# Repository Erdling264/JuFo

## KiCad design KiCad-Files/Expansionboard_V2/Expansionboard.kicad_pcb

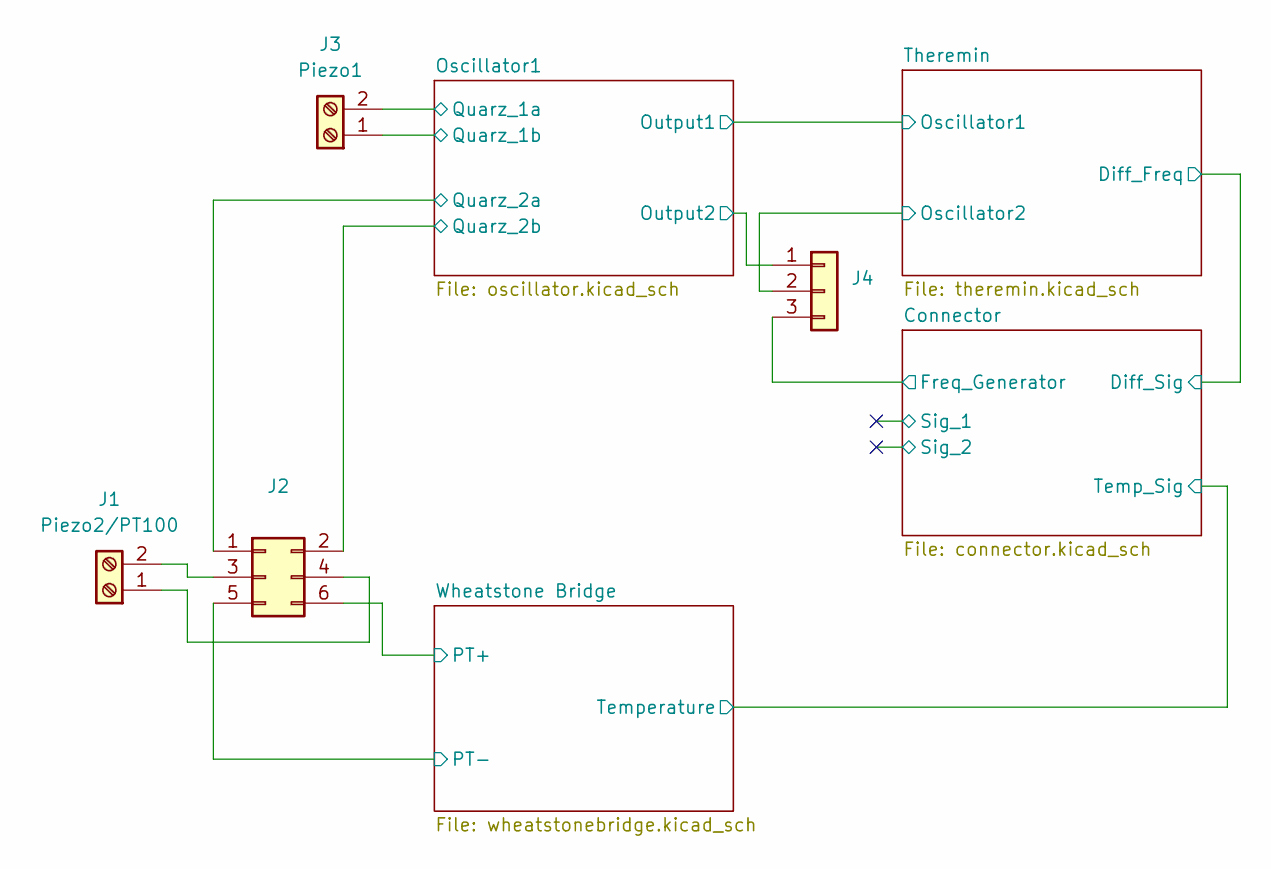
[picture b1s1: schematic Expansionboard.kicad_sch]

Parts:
J1: Piezo2/PT100; TerminalBlock_bornier-2_P5.08mm
J2: Conn_02x03_Odd_Even; PinHeader_2x03_P2.54mm_Vertical
J3: Piezo1; TerminalBlock_bornier-2_P5.08mm
J4: Conn_01x03; PinHeader_1x03_P2.54mm_Vertical

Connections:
/Connector/Freq_Generator: J4.3; also elsewhere on the board
/Oscillator1/Output2: J4.1; also elsewhere on the board
/Oscillator1/Quarz_1a: J3.2; also elsewhere on the board
/Oscillator1/Quarz_1b: J3.1; also elsewhere on the board
/Oscillator1/Quarz_2a: J2.1; also elsewhere on the board
/Oscillator1/Quarz_2b: J2.2; also elsewhere on the board
/Theremin/Oscillator2: J4.2; also elsewhere on the board
/Wheatstone Bridge/PT+: J2.6; also elsewhere on the board
unnamed: J1.1, J2.4
unnamed: J1.2, J2.3
VREF: J2.5; also elsewhere on the board

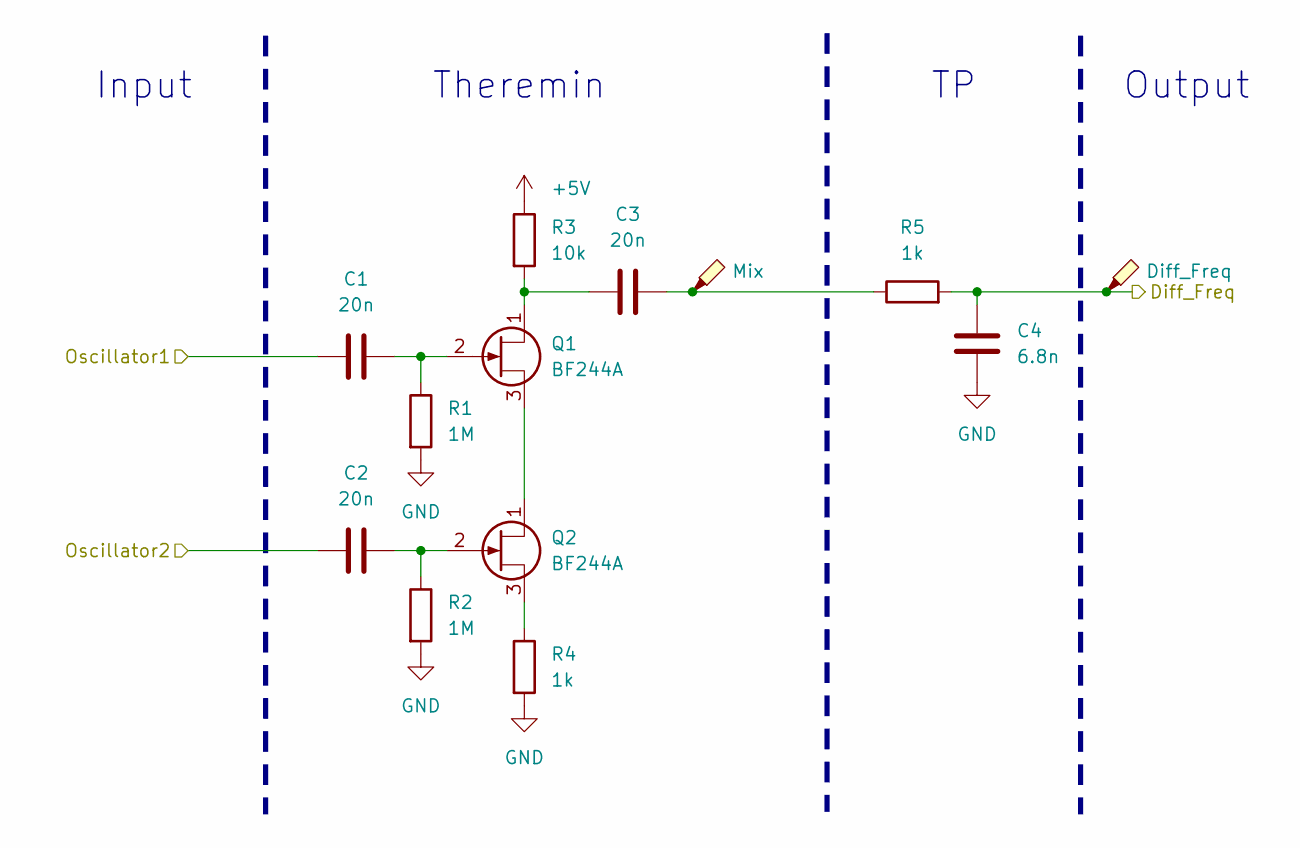
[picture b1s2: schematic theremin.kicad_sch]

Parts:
C1, C2, C3: 20n; C_Disc_D6.0mm_W2.5mm_P5.00mm
C4: 6.8n; C_Disc_D6.0mm_W2.5mm_P5.00mm
Q1, Q2: BF244A; TO-92_Inline
R1, R2: 1M; R_Axial_DIN0207_L6.3mm_D2.5mm_P10.16mm_Horizontal
R3: 10k; R_Axial_DIN0207_L6.3mm_D2.5mm_P10.16mm_Horizontal
R4, R5: 1k; R_Axial_DIN0207_L6.3mm_D2.5mm_P10.16mm_Horizontal
TP1: Mix; TestPoint_Loop_D2.60mm_Drill0.9mm_Beaded
TP2: Diff_Freq; TestPoint_Loop_D2.60mm_Drill0.9mm_Beaded

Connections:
+5V: R3.1; also elsewhere on the board
/Connector/Diff_Sig: C4.2, R5.2, TP2.1; also elsewhere on the board
/Oscillator1/Output1: C1.1; also elsewhere on the board
/Theremin/Oscillator2: C2.1; also elsewhere on the board
GND: C4.1, R1.2, R2.2, R4.2; also elsewhere on the board
unnamed: C3.2, R5.1, TP1.1
unnamed: C3.1, Q1.1 (D), R3.2
unnamed: C1.2, Q1.2 (G), R1.1
unnamed: Q1.3 (S), Q2.1 (D)
unnamed: C2.2, Q2.2 (G), R2.1
unnamed: Q2.3 (S), R4.1

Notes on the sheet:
Theremin
Output
Input

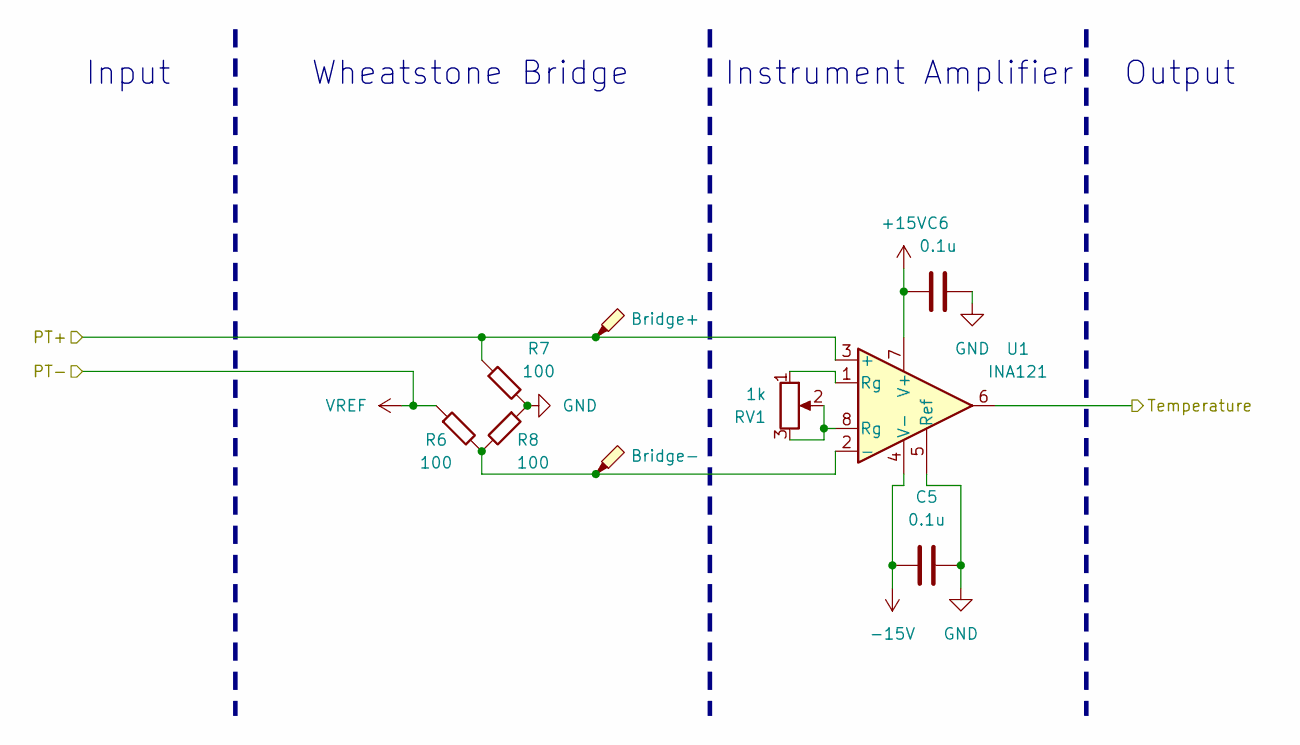
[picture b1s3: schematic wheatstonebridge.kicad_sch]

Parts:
C5, C6: 0.1u; C_Disc_D6.0mm_W2.5mm_P5.00mm
R6, R7, R8: 100; R_Axial_DIN0207_L6.3mm_D2.5mm_P10.16mm_Horizontal
RV1: 1k; Potentiometer_Bourns_3009P_Horizontal
TP3: Bridge+; TestPoint_Loop_D2.60mm_Drill0.9mm_Beaded
TP4: Bridge-; TestPoint_Loop_D2.60mm_Drill0.9mm_Beaded
U1: INA121; DIP-8_W7.62mm_Socket

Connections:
+15V: C6.1, U1.7 (V+); also elsewhere on the board
-15V: C5.1, U1.4 (V-); also elsewhere on the board
/Connector/Temp_Sig: U1.6; also elsewhere on the board
/Wheatstone Bridge/PT+: R7.1, TP3.1, U1.3 (+); also elsewhere on the board
GND: C5.2, C6.2, R7.2, R8.1, U1.5 (Ref); also elsewhere on the board
unnamed: RV1.1, U1.1 (Rg)
unnamed: RV1.2, RV1.3, U1.8 (Rg)
unnamed: R6.2, R8.2, TP4.1, U1.2 (-)
VREF: R6.1; also elsewhere on the board

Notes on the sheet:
Input
Output
Instrument Amplifier
Wheatstone Bridge

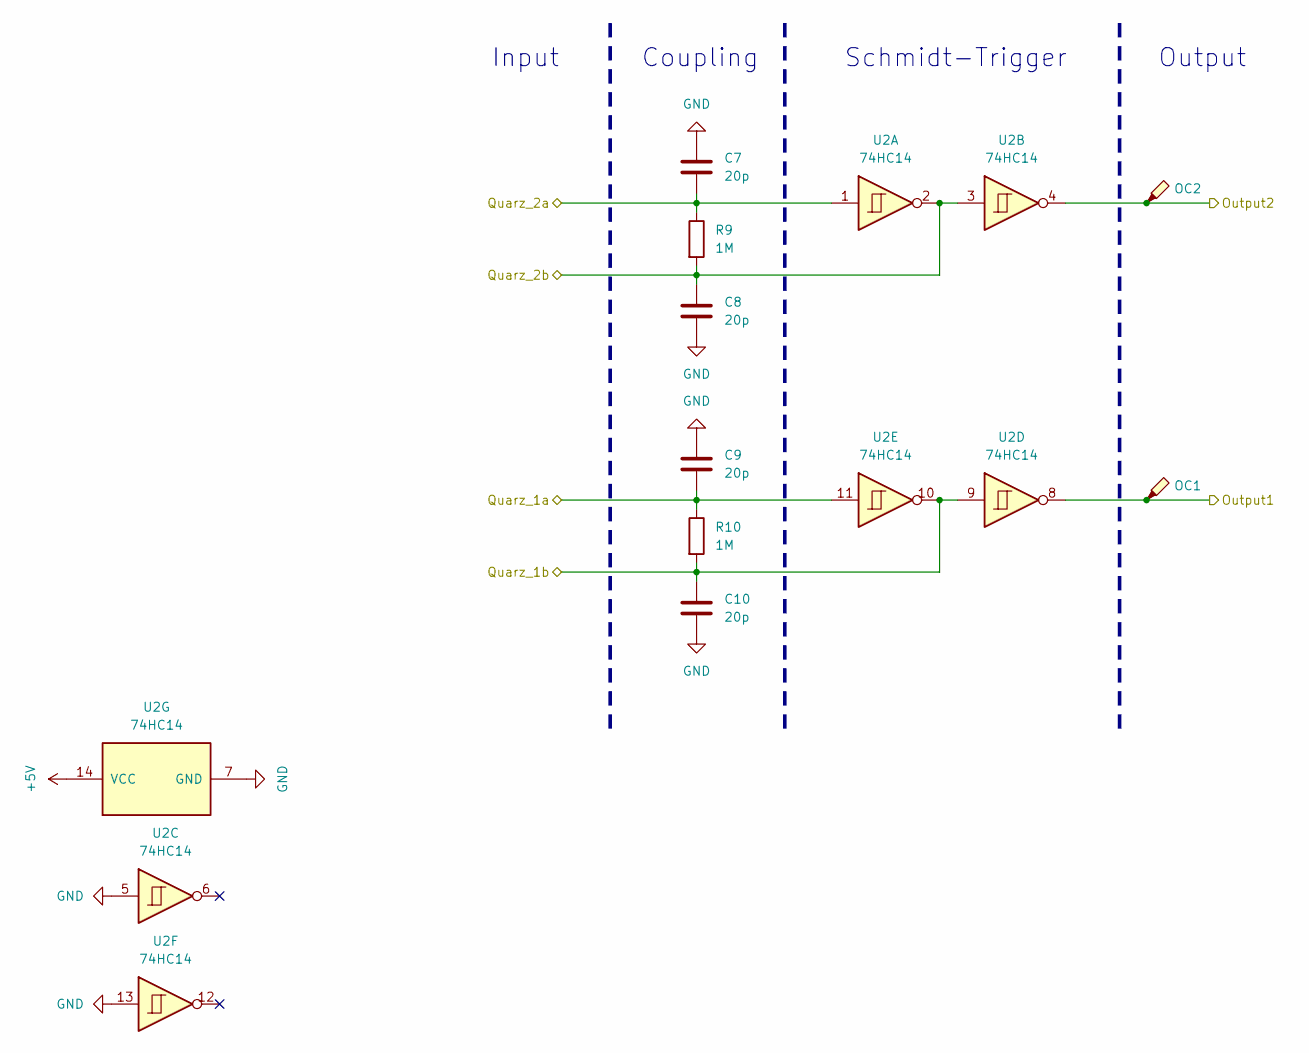
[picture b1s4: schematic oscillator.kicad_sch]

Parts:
C7, C8, C9, C10: 20p; C_Disc_D6.0mm_W2.5mm_P5.00mm
R9, R10: 1M; R_Axial_DIN0207_L6.3mm_D2.5mm_P10.16mm_Horizontal
TP5: OC1; TestPoint_Loop_D2.60mm_Drill0.9mm_Beaded
TP6: OC2; TestPoint_Loop_D2.60mm_Drill0.9mm_Beaded
U2: 74HC14; DIP-14_W7.62mm_Socket

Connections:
+5V: U2.14 (VCC); also elsewhere on the board
/Oscillator1/Output1: TP5.1, U2.8; also elsewhere on the board
/Oscillator1/Output2: TP6.1, U2.4; also elsewhere on the board
/Oscillator1/Quarz_1a: C9.1, R10.1, U2.11; also elsewhere on the board
/Oscillator1/Quarz_1b: C10.2, R10.2, U2.9, U2.10; also elsewhere on the board
/Oscillator1/Quarz_2a: C7.1, R9.1, U2.1; also elsewhere on the board
/Oscillator1/Quarz_2b: C8.2, R9.2, U2.2, U2.3; also elsewhere on the board
GND: C7.2, C8.1, C9.2, C10.1, U2.5, U2.7 (GND), U2.13; also elsewhere on the board

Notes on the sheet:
Schmidt-Trigger
Input
Coupling
Output

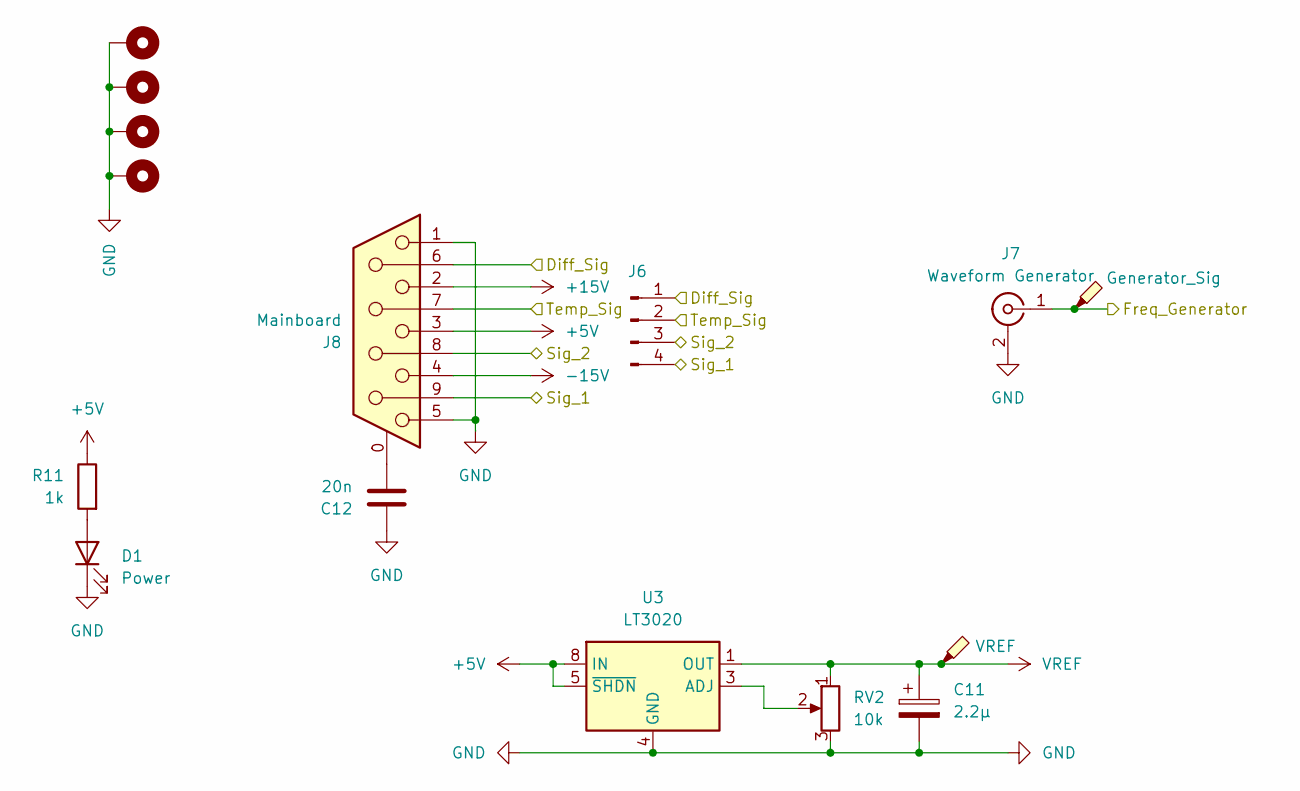
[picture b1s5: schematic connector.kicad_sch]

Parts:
C11: 2.2µ; CP_Radial_D5.0mm_P2.50mm
C12: 20n; C_Disc_D6.0mm_W2.5mm_P5.00mm
D1: Power; LED_D3.0mm_Clear
H1, H2, H3, H4: MountingHole_Pad; MountingHole_4.3mm_M4_DIN965_Pad_TopBottom
J6: Conn_01x04_Pin; PinHeader_1x04_P2.54mm_Vertical
J7: Waveform Generator; BNC_Amphenol_B6252HB-NPP3G-50_Horizontal
J8: Mainboard; DSUB-9_Female_Horizontal_P2.77x2.84mm_EdgePinOffset7.70mm_H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
R11: 1k; R_Axial_DIN0207_L6.3mm_D2.5mm_P10.16mm_Horizontal
RV2: 10k; Potentiometer_Bourns_3009P_Horizontal
TP7: VREF; TestPoint_Loop_D2.60mm_Drill0.9mm_Beaded
TP8: Generator_Sig; TestPoint_Loop_D2.60mm_Drill0.9mm_Beaded
U3: LT3020; MSOP-8-1EP_3x3mm_P0.65mm_EP1.73x1.85mm_ThermalVias

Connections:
+5V: J8.3, R11.1, U3.5 (~SHDN), U3.7 (IN), U3.8 (IN); also elsewhere on the board
+15V: J8.2; also elsewhere on the board
-15V: J8.4; also elsewhere on the board
/Connector/Diff_Sig: J6.1, J8.6; also elsewhere on the board
/Connector/Freq_Generator: J7.1 (In), TP8.1; also elsewhere on the board
/Connector/Sig_1: J6.4, J8.9
/Connector/Sig_2: J6.3, J8.8
/Connector/Temp_Sig: J6.2, J8.7; also elsewhere on the board
GND: C11.2, C12.2, D1.1 (K), H1.1, H2.1, H3.1, H4.1, J7.2 (Ext), J8.1, J8.5, RV2.3, U3.4 (GND), U3.9 (GND); also elsewhere on the board
unnamed: D1.2 (A), R11.2
unnamed: C12.1, J8.0 (PAD)
unnamed: RV2.2, U3.3 (ADJ)
VREF: C11.1, RV2.1, TP7.1, U3.1 (OUT), U3.2 (OUT); also elsewhere on the board

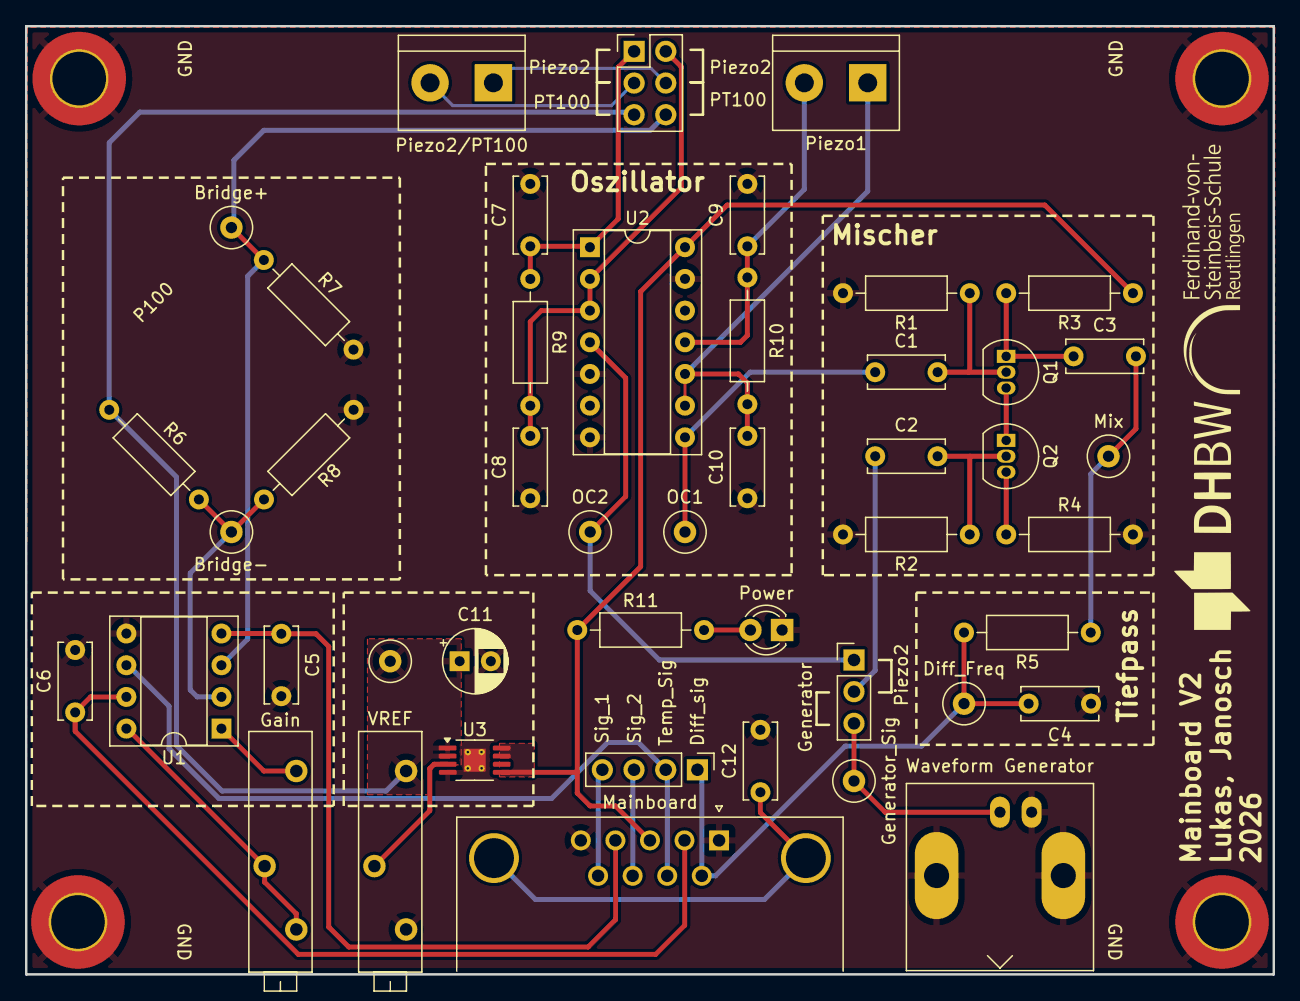
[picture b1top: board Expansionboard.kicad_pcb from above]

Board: 2 copper layers, 100.0 x 76.0 mm, 50 parts (0 on the bottom side), 32 nets.

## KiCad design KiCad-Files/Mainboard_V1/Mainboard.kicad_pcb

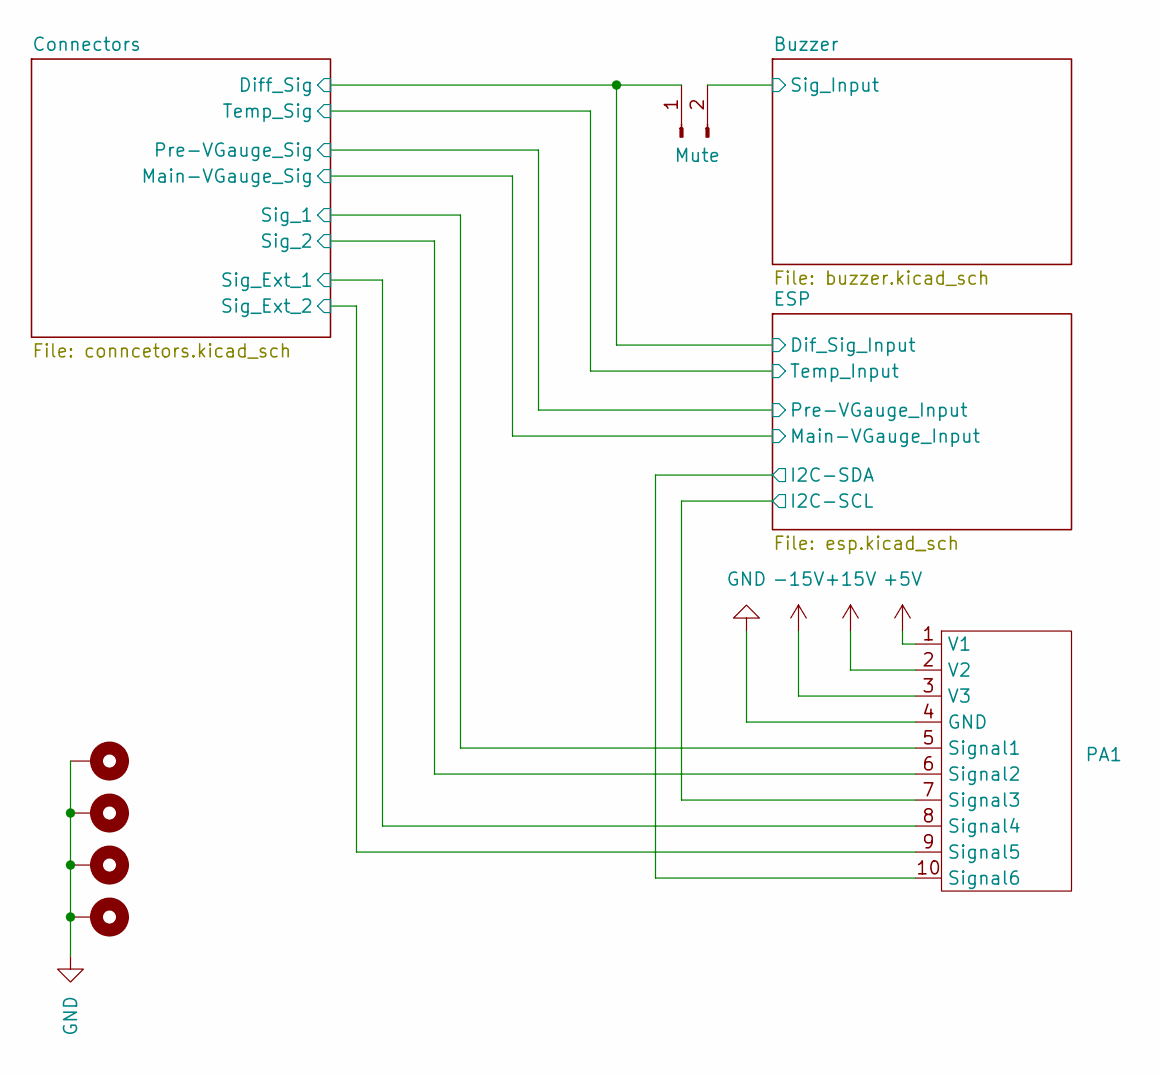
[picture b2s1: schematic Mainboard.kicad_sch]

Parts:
H1, H2, H3, H4: MountingHole_Pad; MountingHole_4.3mm_M4_DIN965_Pad_TopBottom
J1: Mute; PinSocket_1x02_P2.54mm_Vertical
PA1: Prototyping_Area

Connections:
+5V: PA1.1 (V1); also elsewhere on the board
+15V: PA1.2 (V2); also elsewhere on the board
-15V: PA1.3 (V3); also elsewhere on the board
/Buzzer/Sig_Input: J1.2; also elsewhere on the board
/Connectors/Diff_Sig: J1.1; also elsewhere on the board
/Connectors/Sig_1: PA1.5 (Signal1); also elsewhere on the board
/Connectors/Sig_2: PA1.6 (Signal2); also elsewhere on the board
/Connectors/Sig_Ext_1: PA1.8 (Signal4); also elsewhere on the board
/Connectors/Sig_Ext_2: PA1.9 (Signal5); also elsewhere on the board
/ESP/I2C-SCL: PA1.7 (Signal3); also elsewhere on the board
/ESP/I2C-SDA: PA1.10 (Signal6); also elsewhere on the board
GND: H1.1, H2.1, H3.1, H4.1, PA1.4 (GND); also elsewhere on the board

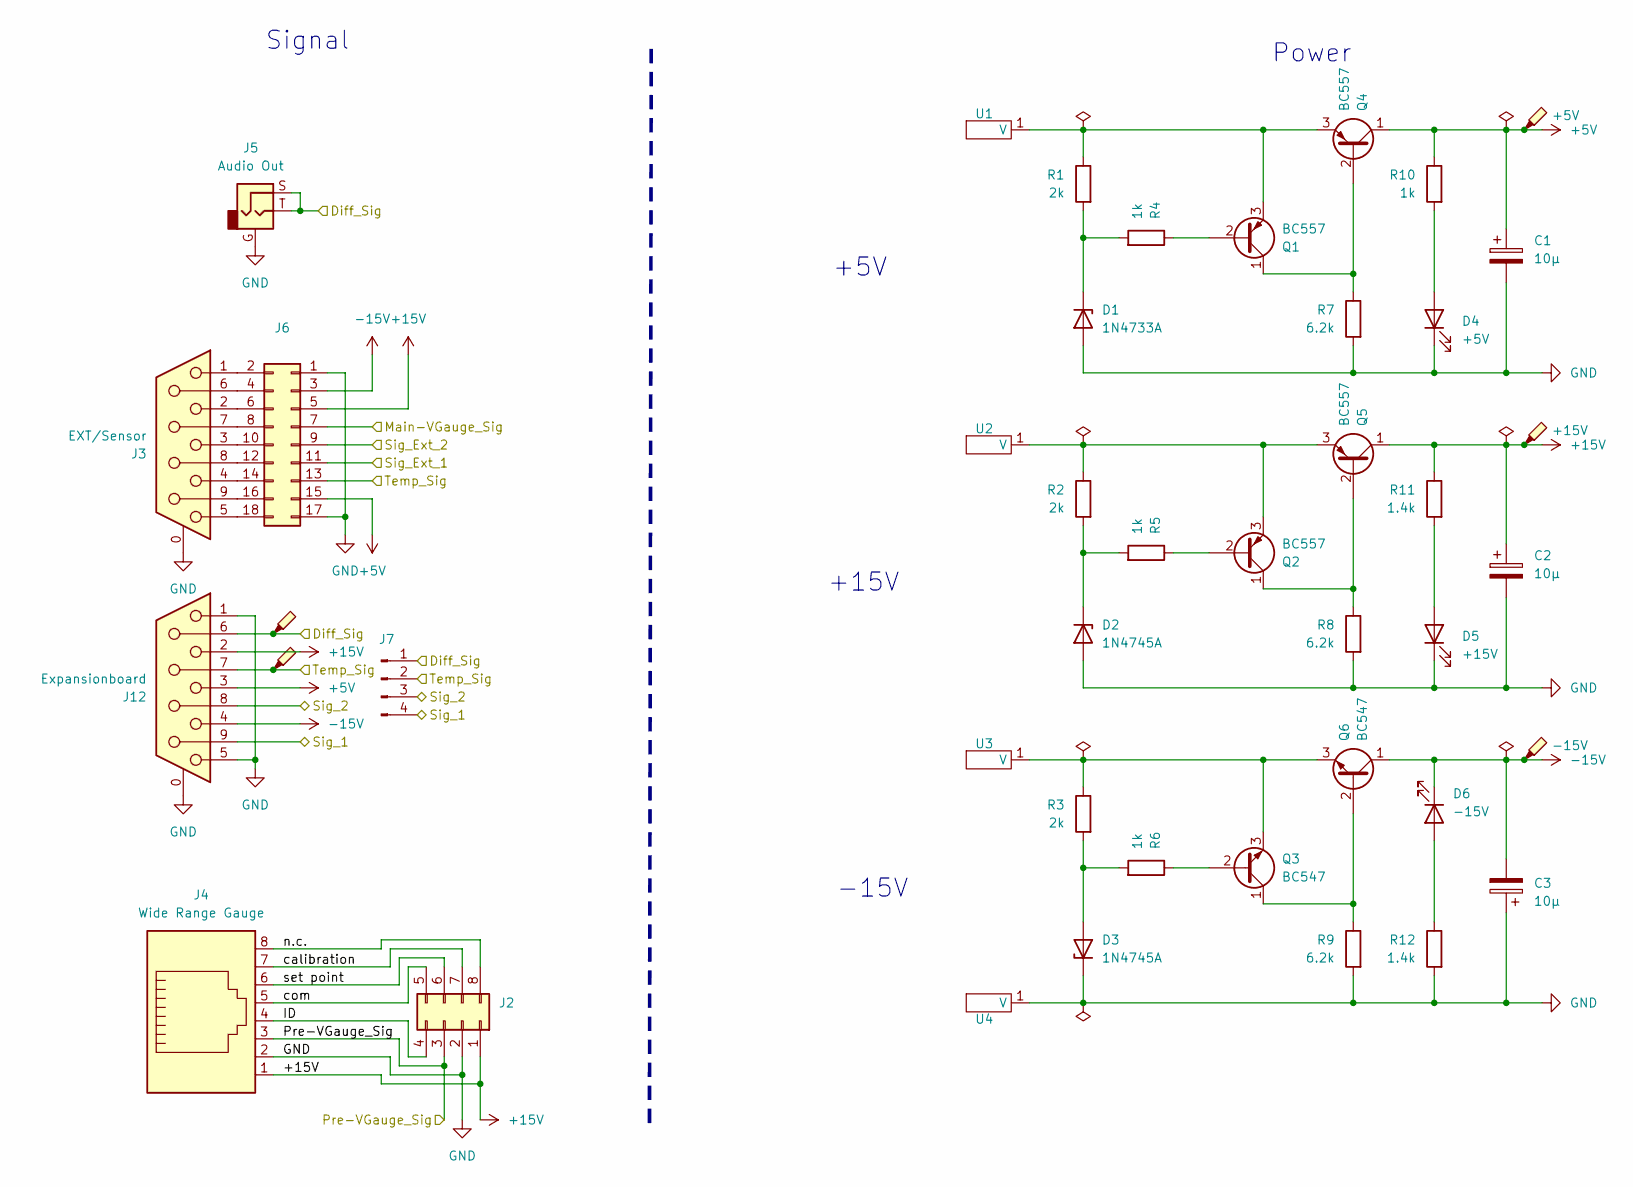
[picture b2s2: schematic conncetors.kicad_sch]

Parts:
C1, C2, C3: 10µ; CP_Radial_D4.0mm_P1.50mm
D1: 1N4733A; D_DO-41_SOD81_P10.16mm_Horizontal
D2, D3: 1N4745A; D_DO-41_SOD81_P10.16mm_Horizontal
D4: +5V; LED_D3.0mm_Clear
D5: +15V; LED_D3.0mm_Clear
D6: -15V; LED_D3.0mm_Clear
J2: Conn_02x04_Counter_Clockwise; PinHeader_2x04_P2.54mm_Vertical
J3: EXT/Sensor; DSUB-9_Female_Horizontal_P2.77x2.84mm_EdgePinOffset7.70mm_H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
J4: Wide Range Gauge; RJ45_OST_PJ012-8P8CX_Vertical
J5: Audio Out; Jack_3.5mm_CUI_SJ1-3523N_Horizontal
J6: Conn_02x09_Odd_Even; PinHeader_2x09_P2.54mm_Vertical
J7: Conn_01x04_Pin; PinHeader_1x04_P2.54mm_Vertical
J12: Expansionboard; DSUB-9_Female_Horizontal_P2.77x2.84mm_EdgePinOffset7.70mm_H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
Q1, Q2, Q4, Q5: BC557; TO-92_Inline
Q3, Q6: BC547; TO-92_Inline
R1, R2, R3: 2k; R_Axial_DIN0207_L6.3mm_D2.5mm_P10.16mm_Horizontal
R4, R5, R6, R10: 1k; R_Axial_DIN0207_L6.3mm_D2.5mm_P10.16mm_Horizontal
R7, R8, R9: 6.2k; R_Axial_DIN0207_L6.3mm_D2.5mm_P10.16mm_Horizontal
R11, R12: 1.4k; R_Axial_DIN0207_L6.3mm_D2.5mm_P10.16mm_Horizontal
TP1: Diff_Sig; TestPoint_Loop_D2.60mm_Drill0.9mm_Beaded
TP2: Temp_Sig; TestPoint_Loop_D2.60mm_Drill0.9mm_Beaded
TP3: +5V; TestPoint_Loop_D2.60mm_Drill0.9mm_Beaded
TP4: +15V; TestPoint_Loop_D2.60mm_Drill0.9mm_Beaded
TP5: -15V; TestPoint_Loop_D2.60mm_Drill0.9mm_Beaded
U1, U2: Banana_Cliff_FCR7350R_S16N-PC_Horizontal
U3: Banana_Cliff_FCR7350L_S16N-PC_Horizontal
U4: Banana_Cliff_FCR7350B_S16N-PC_Horizontal

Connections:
+5V: C1.1, J6.15, J12.3, Q4.1 (C), R10.1, TP3.1; also elsewhere on the board
+15V: C2.1, J2.1, J4.1, J6.5, J12.2, Q5.1 (C), R11.1, TP4.1; also elsewhere on the board
-15V: C3.2, D6.1 (K), J6.3, J12.4, Q6.1 (C), TP5.1; also elsewhere on the board
/Connectors/Diff_Sig: J5.S, J5.T, J7.1, J12.6, TP1.1; also elsewhere on the board
/Connectors/ID: J2.4, J4.4
/Connectors/Main-VGauge_Sig: J6.7; also elsewhere on the board
/Connectors/Pre-VGauge_Sig: J2.3, J4.3; also elsewhere on the board
/Connectors/Sig_1: J7.4, J12.9; also elsewhere on the board
/Connectors/Sig_2: J7.3, J12.8; also elsewhere on the board
/Connectors/Sig_Ext_1: J6.11; also elsewhere on the board
/Connectors/Sig_Ext_2: J6.9; also elsewhere on the board
/Connectors/Temp_Sig: J6.13, J7.2, J12.7, TP2.1; also elsewhere on the board
/Connectors/calibration: J2.7, J4.7
/Connectors/com: J2.5, J4.5
/Connectors/n.c.: J2.8, J4.8
/Connectors/set point: J2.6, J4.6
GND: C1.2, C2.2, C3.1, D1.2 (A), D2.2 (A), D3.1 (K), D4.1 (K), D5.1 (K), J2.2, J3.0 (PAD), J4.2, J5.G, J6.1, J6.17, J12.0 (PAD), J12.1, J12.5, R7.2, R8.2, R9.2, R12.2, U4.1 (V); also elsewhere on the board
unnamed: D1.1 (K), R1.2, R4.2
unnamed: D2.1 (K), R2.2, R5.2
unnamed: D3.2 (A), R3.2, R6.2
unnamed: D4.2 (A), R10.2
unnamed: D5.2 (A), R11.2
unnamed: D6.2 (A), R12.1
unnamed: J3.1, J6.2
unnamed: J3.6, J6.4
unnamed: J3.2, J6.6
unnamed: J3.7, J6.8
unnamed: J3.3, J6.10
unnamed: J3.8, J6.12
unnamed: J3.4, J6.14
unnamed: J3.9, J6.16
unnamed: J3.5, J6.18
unnamed: Q1.2 (B), R4.1
unnamed: Q1.1 (C), Q4.2 (B), R7.1
unnamed: Q1.3 (E), Q4.3 (E), R1.1, U1.1 (V)
unnamed: Q2.2 (B), R5.1
unnamed: Q2.1 (C), Q5.2 (B), R8.1
unnamed: Q2.3 (E), Q5.3 (E), R2.1, U2.1 (V)
unnamed: Q3.2 (B), R6.1
unnamed: Q3.1 (C), Q6.2 (B), R9.1
unnamed: Q3.3 (E), Q6.3 (E), R3.1, U3.1 (V)

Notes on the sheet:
+5V
+15V
Signal
Power
-15V

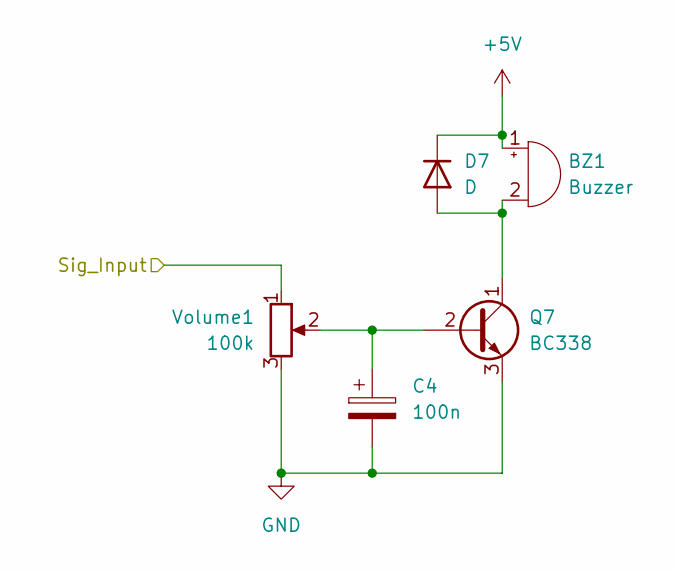
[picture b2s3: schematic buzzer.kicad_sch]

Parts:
BZ1: Buzzer; Buzzer_TDK_PS1240P02BT_D12.2mm_H6.5mm
C4: 100n; CP_Radial_D4.0mm_P1.50mm
D7: D; D_T-1_P10.16mm_Horizontal
Q7: BC338; TO-92
Volume1: 100k; Potentiometer_Omeg_PC16BU_Horizontal

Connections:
+5V: BZ1.1 (+), D7.1 (K); also elsewhere on the board
/Buzzer/Sig_Input: Volume1.1; also elsewhere on the board
GND: C4.2, Q7.3 (E), Volume1.3; also elsewhere on the board
unnamed: BZ1.2 (-), D7.2 (A), Q7.1 (C)
unnamed: C4.1, Q7.2 (B), Volume1.2

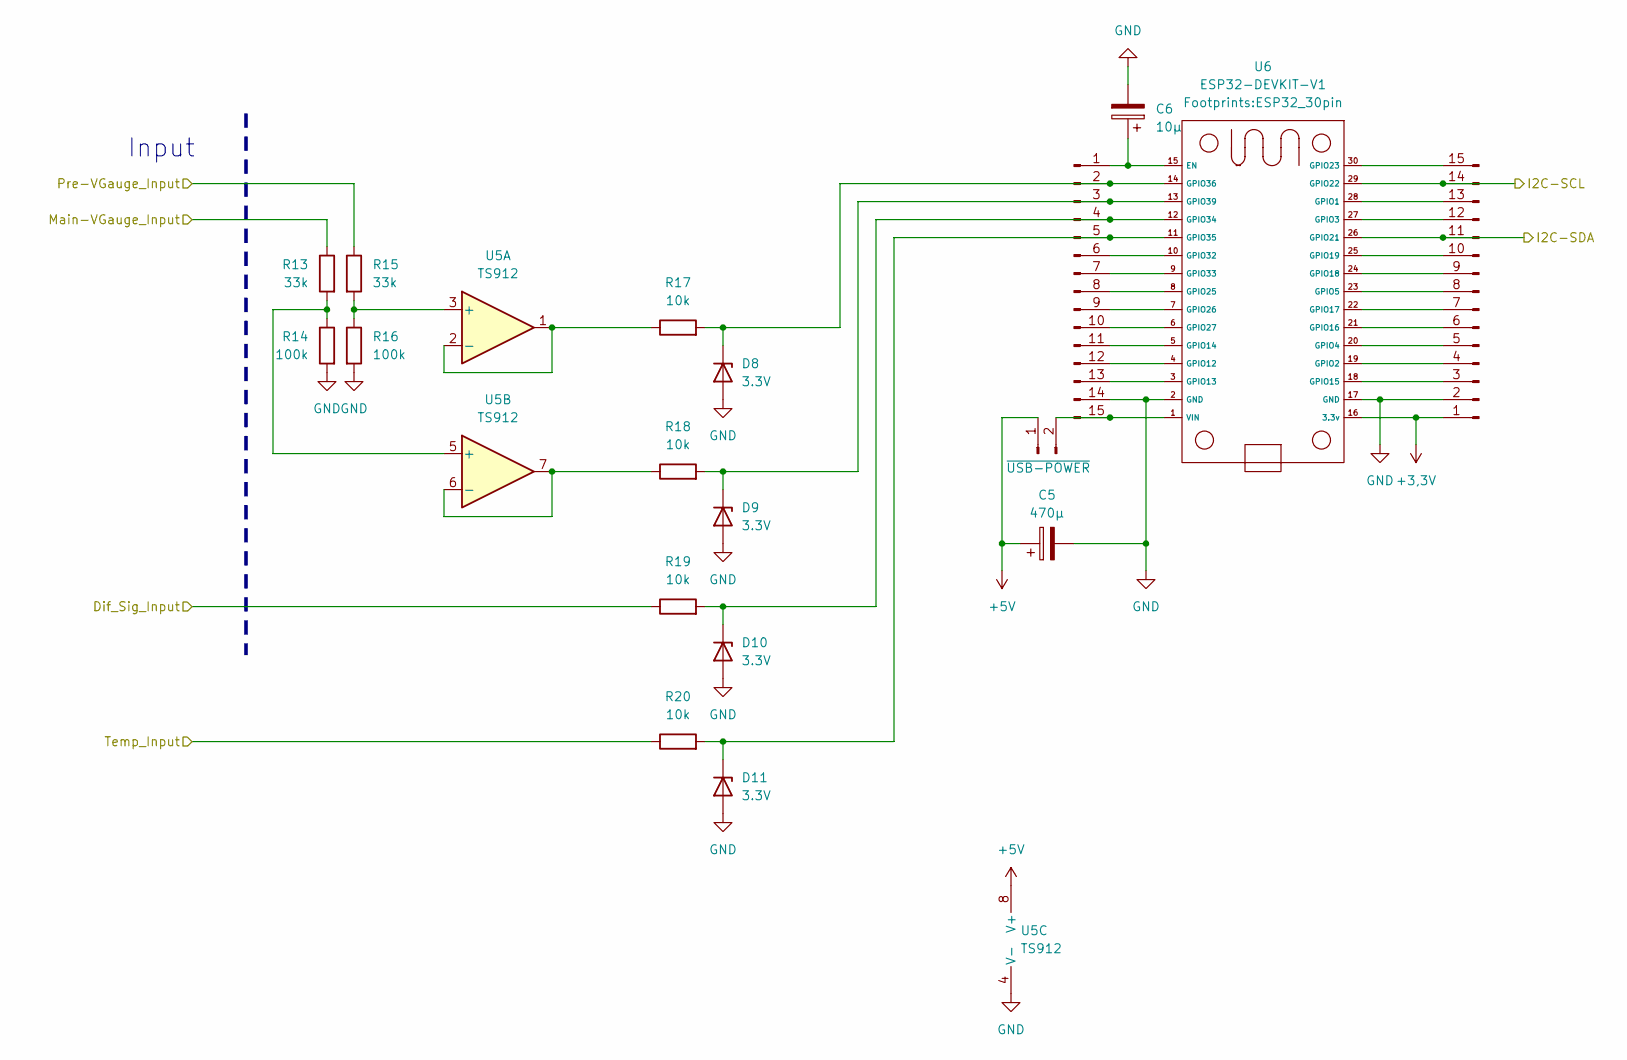
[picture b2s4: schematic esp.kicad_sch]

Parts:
C5: 470µ; CP_Radial_D4.0mm_P1.50mm
C6: 10µ; CP_Radial_D4.0mm_P1.50mm
D8, D9, D10, D11: 3.3V; D_A-405_P10.16mm_Horizontal
J9, J10: Conn_01x15_Pin; PinHeader_1x15_P2.54mm_Vertical
J11: ~{USB-POWER}; PinSocket_1x02_P2.54mm_Vertical
R13, R15: 33k; R_Axial_DIN0207_L6.3mm_D2.5mm_P10.16mm_Horizontal
R14, R16: 100k; R_Axial_DIN0207_L6.3mm_D2.5mm_P10.16mm_Horizontal
R17, R18, R19, R20: 10k; R_Axial_DIN0207_L6.3mm_D2.5mm_P10.16mm_Horizontal
U5: TS912; DIP-8_W7.62mm_Socket
U6: ESP32-DEVKIT-V1; ESP32_30pin

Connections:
+3,3V: J10.1, U6.16 (3.3v)
+5V: C5.1, J11.1, U5.8 (V+); also elsewhere on the board
/Connectors/Diff_Sig: R19.1; also elsewhere on the board
/Connectors/Main-VGauge_Sig: R13.1; also elsewhere on the board
/Connectors/Pre-VGauge_Sig: R15.1; also elsewhere on the board
/Connectors/Temp_Sig: R20.1; also elsewhere on the board
/ESP/I2C-SCL: J10.14, U6.29 (GPIO22); also elsewhere on the board
/ESP/I2C-SDA: J10.11, U6.26 (GPIO21); also elsewhere on the board
GND: C5.2, C6.2, D8.2 (A), D9.2 (A), D10.2 (A), D11.2 (A), J9.14, J10.2, R14.2, R16.2, U5.4 (V-), U6.2 (GND), U6.17 (GND); also elsewhere on the board
unnamed: D8.1 (K), J9.2, R17.2, U6.14 (GPIO36)
unnamed: D9.1 (K), J9.3, R18.2, U6.13 (GPIO39)
unnamed: D10.1 (K), J9.4, R19.2, U6.12 (GPIO34)
unnamed: D11.1 (K), J9.5, R20.2, U6.11 (GPIO35)
unnamed: C6.1, J9.1, U6.15 (EN)
unnamed: J9.6, U6.10 (GPIO32)
unnamed: J9.7, U6.9 (GPIO33)
unnamed: J9.8, U6.8 (GPIO25)
unnamed: J9.9, U6.7 (GPIO26)
unnamed: J9.10, U6.6 (GPIO27)
unnamed: J9.11, U6.5 (GPIO14)
unnamed: J9.12, U6.4 (GPIO12)
unnamed: J9.13, U6.3 (GPIO13)
unnamed: J10.3, U6.18 (GPIO15)
unnamed: J10.4, U6.19 (GPIO2)
unnamed: J10.5, U6.20 (GPIO4)
unnamed: J10.6, U6.21 (GPIO16)
unnamed: J10.7, U6.22 (GPIO17)
unnamed: J10.8, U6.23 (GPIO5)
unnamed: J10.9, U6.24 (GPIO18)
unnamed: J10.10, U6.25 (GPIO19)
unnamed: J10.12, U6.27 (GPIO3)
unnamed: J10.13, U6.28 (GPIO1)
unnamed: J10.15, U6.30 (GPIO23)
unnamed: J9.15, J11.2, U6.1 (VIN)
unnamed: R15.2, R16.1, U5.3 (+)
unnamed: R17.1, U5.1, U5.2 (-)
unnamed: R13.2, R14.1, U5.5 (+)
unnamed: R18.1, U5.6 (-), U5.7

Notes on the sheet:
Input

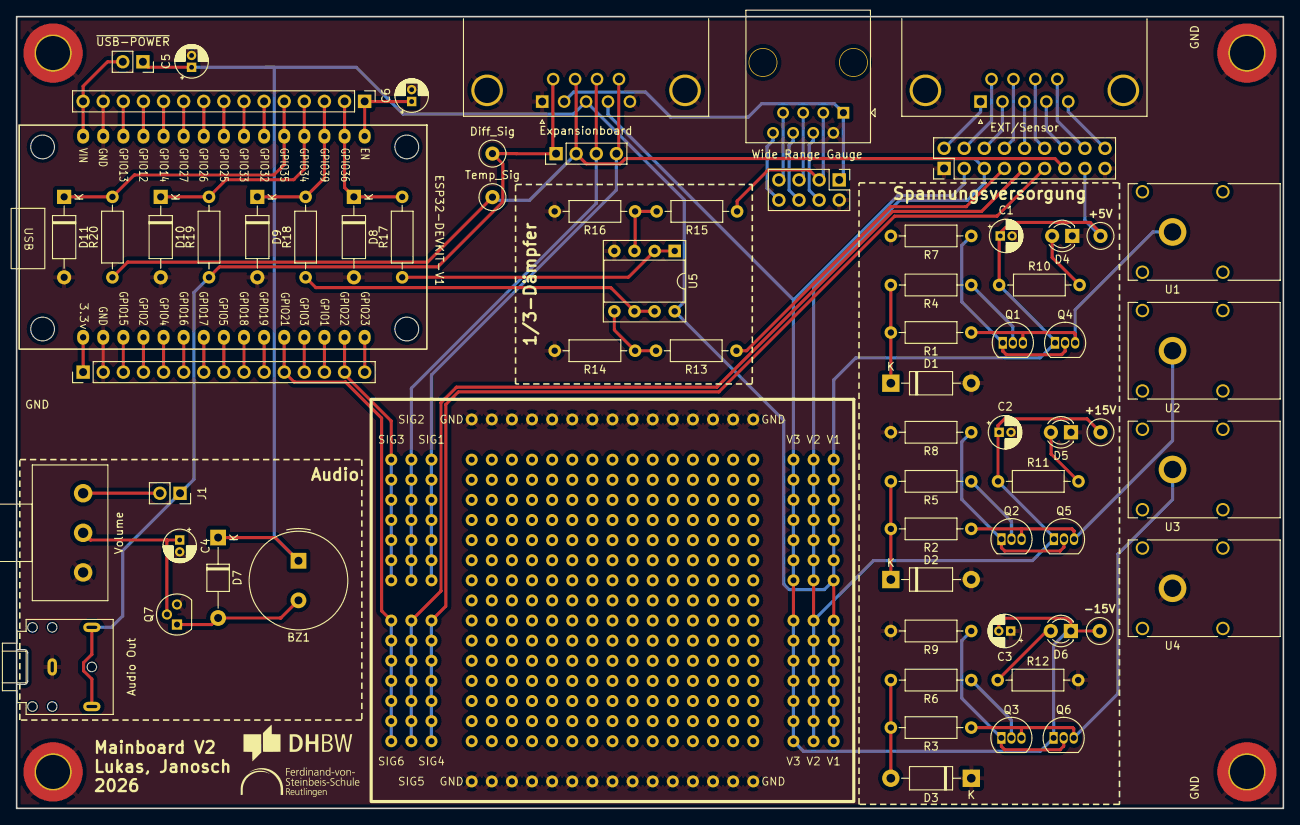
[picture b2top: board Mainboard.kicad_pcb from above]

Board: 2 copper layers, 160.0 x 100.0 mm, 73 parts (1 on the bottom side), 76 nets.

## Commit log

2026-02-09 Uploaded KiCad-Files
